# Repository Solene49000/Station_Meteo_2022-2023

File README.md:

INTRODUCTION
-
Dans le cadre du projet de la ruche connectée, nous continuons le développement de la station météo.
Celle ci permet  la mesure de données météorologiques telles que :
- La quantité de pluie tombée (1 front montant par basculement du pluviomètre)
- La vitesse du vent (1 front montant par tour d'anémomètre)
- La direction du vent (Tension différente par direction)
- La luminosité (I2C)
- La température (I2C)
- L'humidité (I2C)

Le code final nommé **test_sleep** est situé dans le repertoire : *Codes/Dernière version* : [https://github.com/Solene49000/Station_Meteo_2022-2023/tree/main/Codes/Derni%C3%A8re_version/test_sleep]

1 - LES PORTS
-

- Les ports LoRa
  - SCK : 18 -- Horloge SPI
  - MISO : 19 -- Master In Slave Out SPI
  - MOSI : 23 -- Master Out Slave In SPI
  - SS : 5 -- Select Slave = NSS SPI
  - RST : 14 -- Reset
  - DI0 : 26 -- Données
  
- Les ports de modules
  - ANEMOMETRE : 27 -- Récupère données anémomètre
  - PLUVIOMETRE : 32 -- Récupère données pluviomètre
  - GIROUETTE : 36 -- Récupère données girouette

- Autres ports
  - MEASURE : 13 -- Mettre à high pour fournir une tension aux modules
  - LED_R : 33 -- Led rouge de test du bon fonctionnement
  - LED_G : 25 -- Led verte de test du bon fonctionnement

2- LES FICHIERS
-
- test_sleep.ino : Demande à des fréquences régulières la restitution des données des modules et envoie la trame LoRa
- Girouette.ino : Renvoie la direction du vent entre 0 et 15 ( 0 = Nord, 1 = Nord Nord Ouest, ...)
- Anemometre.ino : Renvoie la vitesse du vent jusquà 250 km/h (float)
- Pluviometre.ino : Renvoie la quantité d'eau tombée en 10s
- LuxHumTemp.ino : 
  - Renvoie la luminosité en lux
  - Renvoie l'humidité en pourcentage
  - Renvoie la température en degrés
- ESP_LoRa_internal.ino : 
  - Appelle 3 fonctions
    - build_trame : écrit une trame avec les données brutes de nos mesures
    - debug_trame : reformate la trame en binaire
    - lora_send_trame : envoie la trame vers l'antenne
- Batterie.ino : Renvoie la tension de la batterie
 
3 - LES DETAILS
-
- Une trame LoRa est envoyée toutes les 15 minutes
- Structure trame :   I|macAdresse|pluviomètre|anémomètre|girouette|partie_1_pression|partie_2_pression|humidité|luminosité|température|batterie|checkbytes

4 - LE SET UP
-
- Télécharger Arduino IDE
- Télécharger toutes les librairies affichées dans le fichier concerné
- Paramétrer Arduino IDE pour accepter la carte ESP32 Dev Module
- Copier le code issu de github : ouvrir le terminal de commande, allez dans votre répertoire du projet et entrez la fonction suivante "git copy https://github.com/Solene49000/Station_Meteo_2022-2023/tree/main/Codes"
- Dans documents, ouvrir le fichier "Station_meteo.ino". Tous les fichiers du dossier s'ouvrent dans Arduino
- Préparer le set up :
  - Brancher le pluviomètre au connecteur P
  - Brancher l'anémomètre et la girouette au connecteur G
  - Brancher le câble USB à la carte Arduino et à votre PC
- Compiler puis téléverser le code ( La compilation peut s'avérer très longue car Arduino n'est pas vraiment adapté à Windows et nous avons un certain nombre de fichiers)

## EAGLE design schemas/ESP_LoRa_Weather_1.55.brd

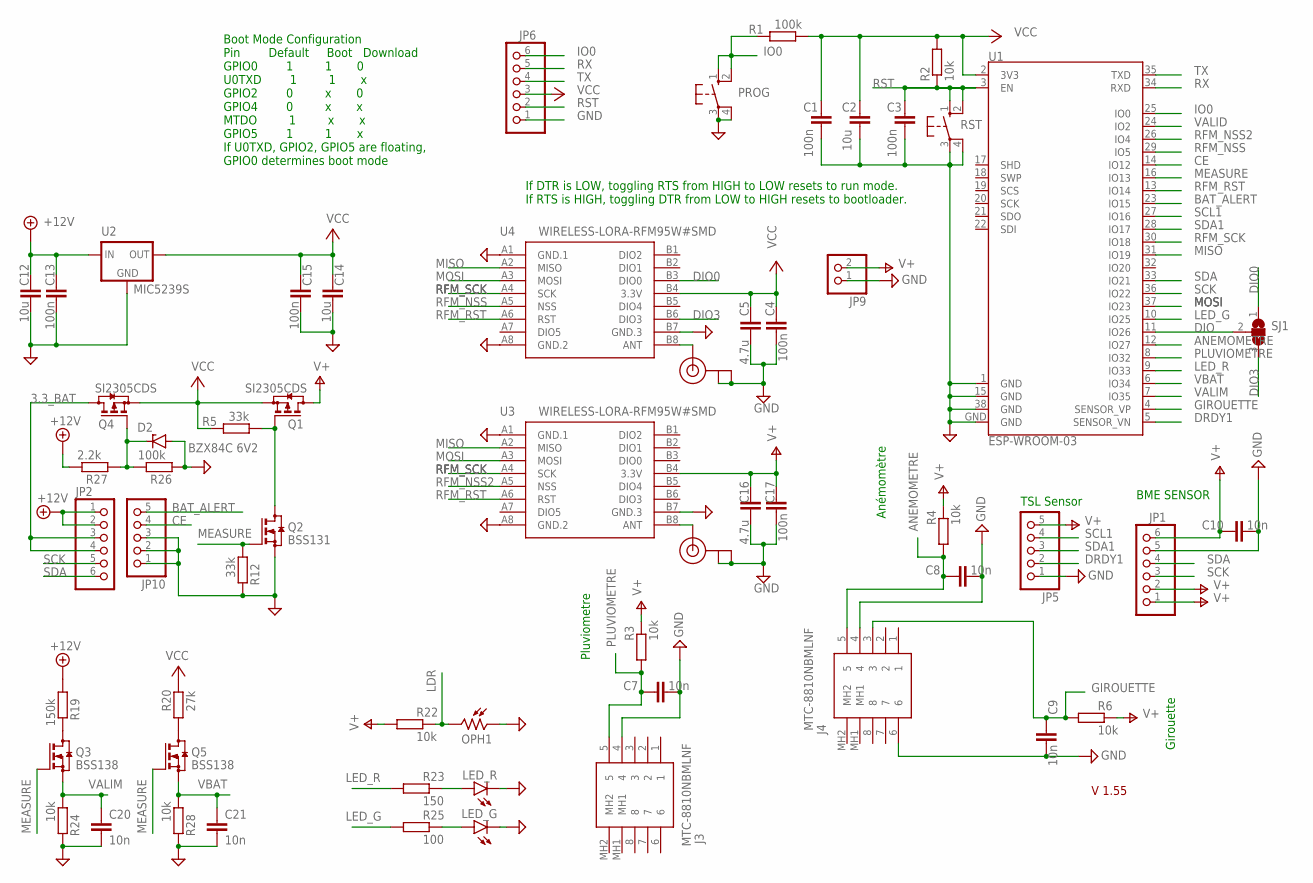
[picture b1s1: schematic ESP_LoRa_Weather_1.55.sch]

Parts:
C1, C3, C4, C13, C15, C17: 100n; C1206
C2, C12, C14: 10u; C1210
C5, C16: 4.7u; C1210
C7, C8, C9, C10, C20, C21: 10n; C1206
D2: BZX84C 6V2; TO236
J1, J2: U.FL
J3, J4: MTC-8810NBMLNF; MTC8810NBMLNF
JP1, JP2, JP6: PINHD-1X6; 1X06
JP5, JP10: PINHD-1X5; 1X05
JP9: PINHD-1X2; 1X02
LED_G: LEDSMT1206; 1206
LED_R: LEDSMT1206; 1206
OPH1: VT93N2; VT900
PROG: 10-XX; B3F-10XX
Q1, Q4: SI2305CDS; SOT23
Q2: BSS131; SOT23
Q3, Q5: BSS138; SOT23
R1, R26: 100k; R1206
R2, R3, R4, R6, R22, R24, R28: 10k; R1206
R5, R12: 33k; R1206
R19: 150k; R1206
R20: 27k; R1206
R23: 150; R1206
R25: 100; R1206
R27: 2.2k; R1206
RST: 10-XX; B3F-10XX
SJ1: SJ2W; SJ_2
U1: ESP-WROOM-03
U2: MIC5239S; SOT223
U3, U4: WIRELESS-LORA-RFM95W#SMD

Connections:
3.3_BAT: JP2.3, JP2.4, Q4.3 (D)
+12V: C12.1, C13.1, JP2.1, JP2.2, R19.1, R27.2, U2.1 (IN)
ANEMOMETRE: C8.1, J4.5, R4.1, U1.12 (IO27)
ANT2: J2.3 (SIGNAL), U4.B8 (ANT)
ANT3: J1.3 (SIGNAL), U3.B8 (ANT)
BAT_ALERT: JP10.5, U1.23 (IO15)
CE: JP10.4, U1.14 (IO12)
DIO: SJ1.2, U1.11 (IO26)
DIO0: SJ1.1, U4.B3 (DIO0)
DIO3: SJ1.3, U4.B6 (DIO3)
DRDY1: JP5.2, U1.5 (SENSOR_VN)
GIROUETTE: C9.1, J4.3, R6.1, U1.4 (SENSOR_VP)
GND: C1.2, C2.2, C3.2, C4.2, C5.2, C7.2, C8.2, C9.2, C10.2, C12.2, C13.2, C14.2, C15.2, C16.2, C17.2, C20.2, C21.2, D2.A, J1.1 (GND), J1.2 (GND), J2.1 (GND), J2.2 (GND), J3.4, J4.4, J4.6, JP1.5, JP5.1, JP6.1, JP9.1, JP10.1, JP10.2, JP10.3, LED_G.C, LED_R.C, OPH1.1, PROG.3, PROG.4 (P1), Q2.2 (S), R12.2, R24.2, R26.1, R28.2, RST.3, RST.4 (P1), U1.1 (GND), U1.15 (GND), U1.38 (GND), U1.GND, U2.2 (GND), U2.4 (GND), U3.A1 (GND.1), U3.A8 (GND.2), U3.B7 (GND.3), U4.A1 (GND.1), U4.A8 (GND.2), U4.B7 (GND.3)
IO0: JP6.6, PROG.1 (S), PROG.2 (S1), R1.2, U1.25 (IO0)
LDR: OPH1.2, R22.2
LED_G: R25.1, U1.10 (IO25)
LED_R: R23.1, U1.9 (IO33)
MEASURE: Q2.1 (G), Q3.1 (G), Q5.1 (G), R12.1, U1.16 (IO13)
MISO: U1.31 (IO19), U3.A2 (MISO), U4.A2 (MISO)
MOSI: U1.37 (IO23), U3.A3 (MOSI), U4.A3 (MOSI)
unnamed: Q1.1 (G), Q2.3 (D), R5.1
unnamed: Q3.3 (D), R19.2
unnamed: Q5.3 (D), R20.1
unnamed: LED_R.A, R23.2
unnamed: LED_G.A, R25.2
unnamed: D2.C, Q4.1 (G), R26.2, R27.1
PLUVIOMETRE: C7.1, J3.5, R3.1, U1.8 (IO32)
RFM_NSS: U1.29 (IO5), U4.A5 (NSS)
RFM_NSS2: U1.26 (IO4), U3.A5 (NSS)
RFM_RST: U1.13 (IO14), U3.A6 (RST), U4.A6 (RST)
RFM_SCK: U1.30 (IO18), U3.A4 (SCK), U4.A4 (SCK)
RST: C3.1, JP6.2, R2.1, RST.1 (S), RST.2 (S1), U1.3 (EN)
RX: JP6.5, U1.34 (RXD)
SCK: JP1.3, JP2.5, U1.36 (IO22)
SCL1: JP5.4, U1.27 (IO16)
SDA: JP1.4, JP2.6, U1.33 (IO21)
SDA1: JP5.3, U1.28 (IO17)
TX: JP6.4, U1.35 (TXD)
V+: C10.1, C16.1, C17.1, JP1.1, JP1.2, JP1.6, JP5.5, JP9.2, Q1.3 (D), R3.2, R4.2, R6.2, R22.1, U3.B4 (3.3V)
VALID: U1.24 (IO2)
VALIM: C20.1, Q3.2 (S), R24.1, U1.7 (IO35)
VBAT: C21.1, Q5.2 (S), R28.1, U1.6 (IO34)
VCC: C1.1, C2.1, C4.1, C5.1, C14.1, C15.1, JP6.3, Q1.2 (S), Q4.2 (S), R1.1, R2.2, R5.2, R20.2, U1.2 (3V3), U2.3 (OUT), U4.B4 (3.3V)

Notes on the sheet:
If DTR is LOW, toggling RTS from HIGH to LOW resets to run mode. If RTS is HIGH, toggling DTR from LOW to HIGH resets to bootloader.
Boot Mode Configuration Pin Default Boot Download GPIO0 1 1 0 U0TXD 1 1 x GPIO2 0 x 0 GPIO4 0 x x MTDO 1 x x GPIO5 1 1 x If U0TXD, GPIO2, GPIO5 are floating, GPIO0 determines boot mode
V 1.55
TSL Sensor
BME SENSOR
Pluviometre
Anémomètre
Girouette

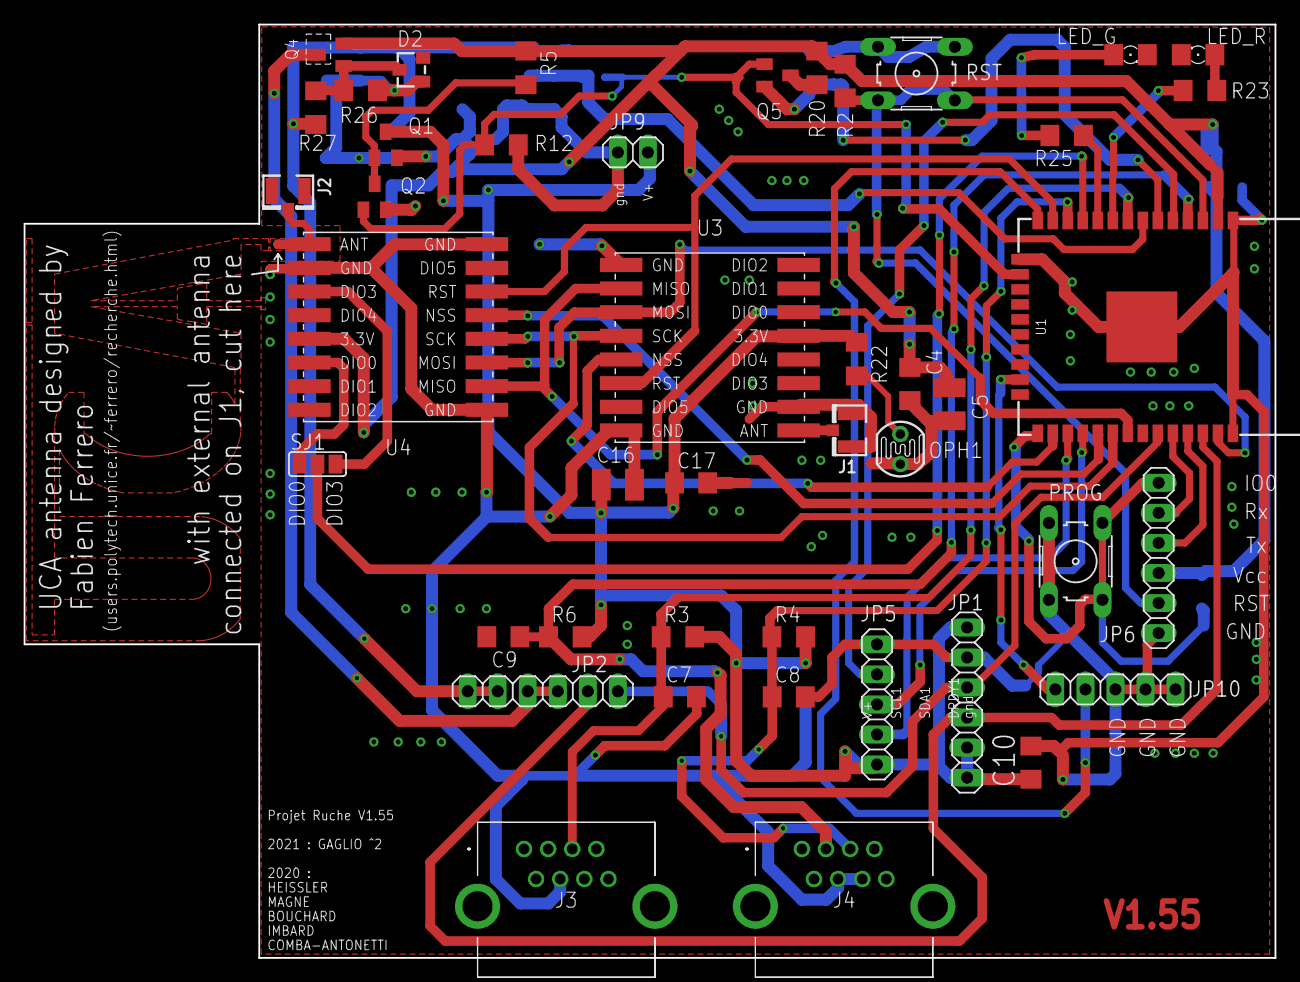
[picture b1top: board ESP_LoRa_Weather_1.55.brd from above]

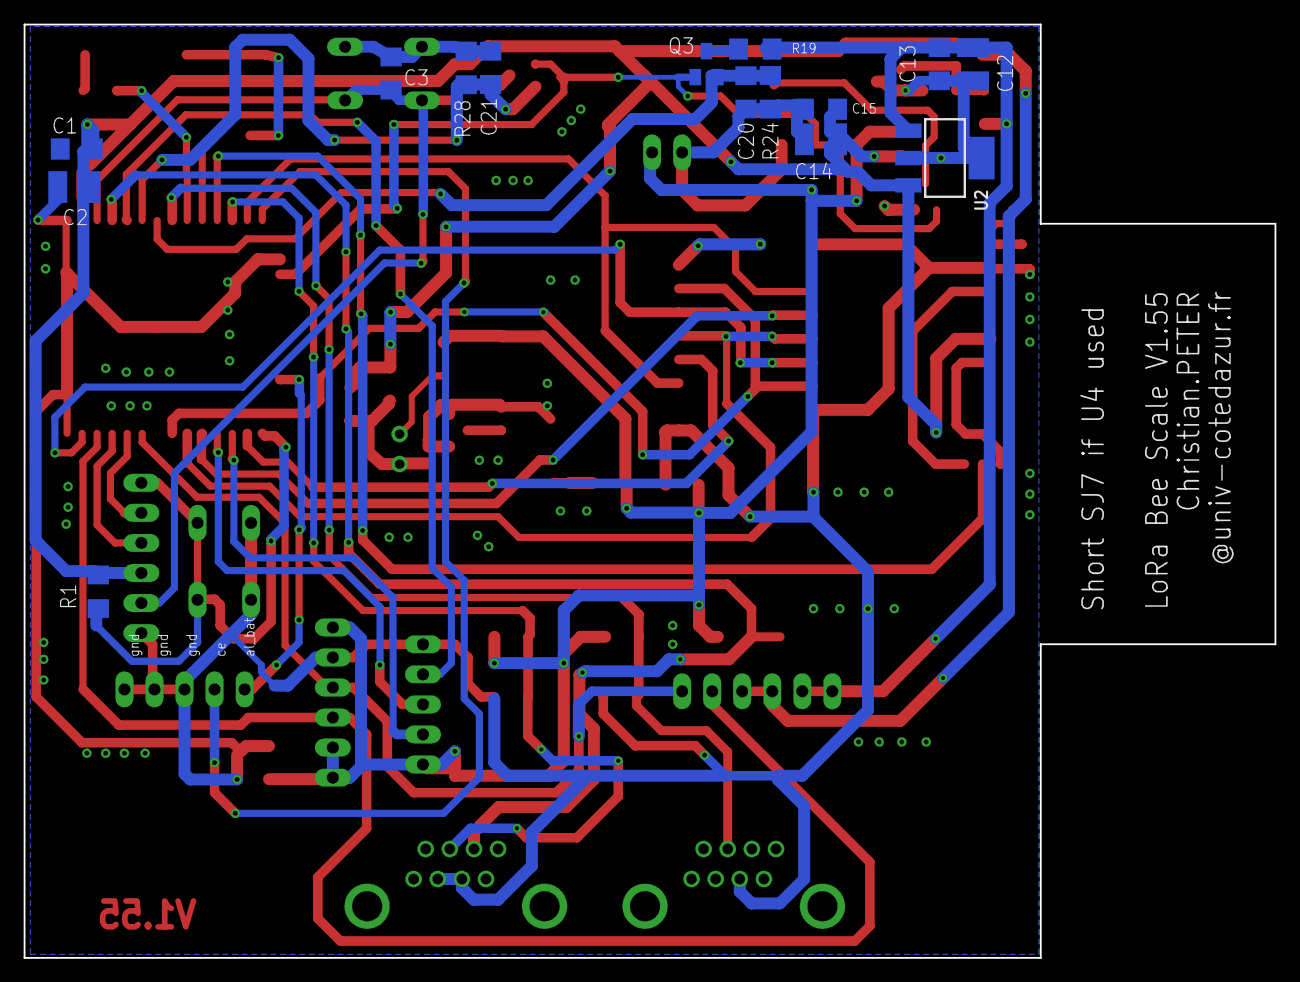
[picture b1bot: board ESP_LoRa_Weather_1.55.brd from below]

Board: 2 copper layers, 105.8 x 78.9 mm, 59 parts (15 on the bottom side), 42 nets.

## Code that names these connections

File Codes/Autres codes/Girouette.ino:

#define MEASURE 13
#define LED_R 33
#define LED_G 25
//#define ANEMOMETRE 12
//#define PLUVIOMETRE 8
#define GIROUETTE 36
//#define GIROUETTE 32

void setup() {
  pinMode(MEASURE, OUTPUT);
  digitalWrite(MEASURE, HIGH);
  pinMode (LED_R, OUTPUT);
  pinMode (LED_G, OUTPUT);
//pinMode (ANEMOMETRE, OUTPUT);
//pinMode (PLUVIOMETRE, OUTPUT);
  pinMode (GIROUETTE, INPUT);
  Serial.begin(9600);
}

void loop() {
  
  digitalWrite(LED_G, HIGH);
  delay(100);
  digitalWrite(LED_G, LOW);
  delay(100);

  int sensorValue = analogRead(GIROUETTE);
  String directionVent;
  if (sensorValue > 3216 && sensorValue <= 3600 )
  {
    directionVent = "Ouest";
  }
  if (sensorValue > 2869 && sensorValue <= 3216)
  {
    directionVent = "Nord Ouest";
  }
  if (sensorValue > 2646 && sensorValue <= 2869)
  {
    directionVent = "Nord Ouest Ouest";
  }
  if (sensorValue > 2417 && sensorValue <= 2646)
  {
    directionVent = "Nord";
  }
  if (sensorValue > 2121 && sensorValue <= 2417)
  {
    directionVent = "Nord Nord Ouest";
  }
  if (sensorValue > 1934 && sensorValue <= 2121)
  {
    directionVent = "Sud Ouest";
  }
  if (sensorValue > 1645 && sensorValue <= 1934)
  {
    directionVent = "Sud Ouest Ouest";
  }
  if (sensorValue > 1312 && sensorValue <= 1645)
  {
    directionVent = "Nord Est";
  }
  if (sensorValue > 1008 && sensorValue <= 1312)
  {
    directionVent = "Nord Nord Est";
  }
  if (sensorValue > 725 && sensorValue <= 1008)
  {
    directionVent = "Sud";
  }
  if (sensorValue > 543 && sensorValue <= 725)
  {
    directionVent = "Sud Sud Ouest";
  }
  if (sensorValue > 338 && sensorValue <= 543)
  {
    directionVent = "Sud Est";
  }
  if (sensorValue > 184 && sensorValue <= 338)
  {
    directionVent = "Sud Sud Est";
  }
  if (sensorValue > 111 && sensorValue <= 184)
  {
    directionVent = "Est";
  }
  if (sensorValue > 64 && sensorValue <= 111)
  {
    directionVent = "Nord Est Est";
  }
  if (sensorValue > 1 && sensorValue <= 64)
  {
    directionVent = "Sud Est Est";
  }
  Serial.print("Direction du vent : ");
  Serial.println(directionVent);
}

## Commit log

2022-09-01 Create SoleneGUILLAUME.md
    Cahier de bord du projet Ruche connectée Module météo de Solene Guillaume
2022-09-01 Create Documentation
2022-09-01 Create bla
2022-09-01 Create test
2022-09-01 Rename SoleneGUILLAUME.md to Rapports de séance/SoleneGUILLAUME.md
2022-09-01 Rename AmbreALLOUIS.md to Rapports de séance/AmbreALLOUIS.md
2022-09-09 Rename LedTest.ino to Codes/LedTest.ino
2022-12-01 Add files via upload
    Code girouette OK
2022-12-01 Create Liste des bibliothèques
2022-12-02 Update Liste des bibliothèques
2022-12-02 Rename Liste des bibliothèques to Liste des bibliothèques.md
2023-01-06 Create README.md
    Explication des ports
2023-04-06 Ajout de périphériques
2023-04-20 Create blabla
2023-04-20 Create b
2023-05-29 Create Rapport_&_Presentation

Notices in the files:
parts and their libraries:
diy-modules: Released under the Creative Commons Attribution 4.0 International License: http://creativecommons.org/licenses/by/4.0
micrel: Copyright (C) 2008, Bob Starr
